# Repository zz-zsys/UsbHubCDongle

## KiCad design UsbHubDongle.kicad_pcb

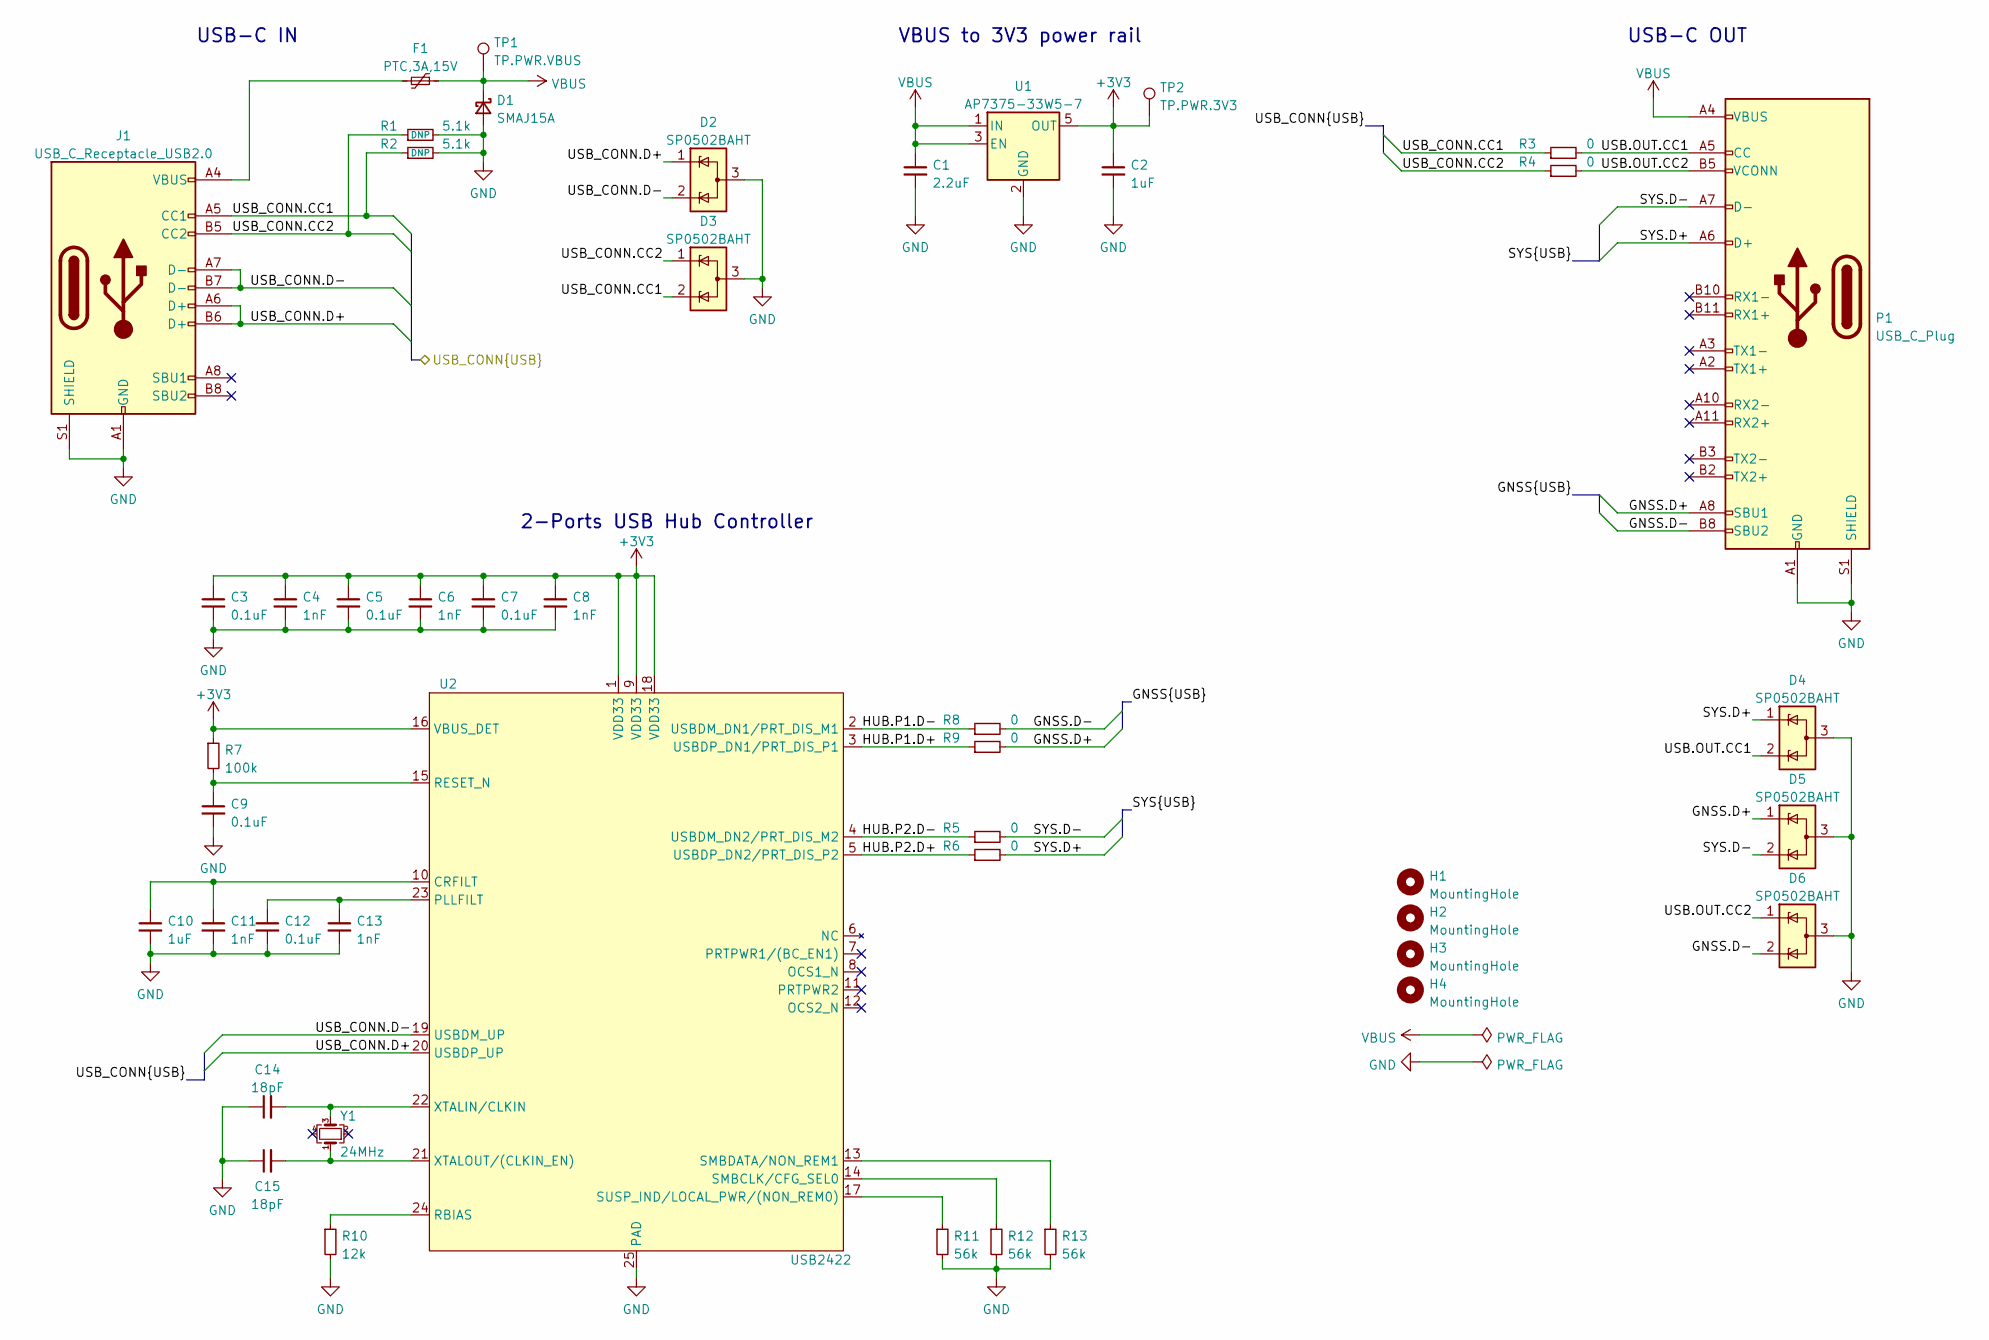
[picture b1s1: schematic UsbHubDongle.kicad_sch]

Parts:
C1: 2.2uF; C_0603_1608Metric
C2, C10: 1uF; C_0603_1608Metric
C3, C5, C7, C9, C12: 0.1uF; C_0603_1608Metric
C4, C6, C8, C11, C13: 1nF; C_0603_1608Metric
C14, C15: 18pF; C_0603_1608Metric
D1: SMAJ15A; D_SMA
D2, D3, D4, D5, D6: SP0502BAHT; SOT-23
F1: PTC,3A,15V; Fuse_2920_7451Metric
H1, H2, H3, H4: MountingHole; MountingHole_2.7mm_M2.5
J1: USB_C_Receptacle_USB2.0; USB_C_Receptacle_GCT_USB4105-xx-A_16P_TopMnt_Horizontal
P1: USB_C_Plug; USB_C_Plug_GCT_USB4155-03-C
R1, R2: 5.1k; R_0603_1608Metric
R3, R4, R5, R6, R8, R9: 0; R_0603_1608Metric
R7: 100k; R_0603_1608Metric
R10: 12k; R_0603_1608Metric
R11, R12, R13: 56k; R_0603_1608Metric
TP1: TP.PWR.VBUS; TestPoint_Loop_D1.80mm_Drill1.0mm_Beaded
TP2: TP.PWR.3V3; TestPoint_Loop_D1.80mm_Drill1.0mm_Beaded
U1: AP7375-33W5-7; SOT-23-5
U2: USB2422; QFN-24-1EP_4x4mm_P0.5mm_EP2.5x2.5mm_ThermalVias
Y1: 24MHz; Crystal_SMD_2016-4Pin_2.0x1.6mm

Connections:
+3V3: C2.1, C3.1, C4.1, C5.1, C6.1, C7.1, C8.1, R7.1, TP2.1, U1.5 (OUT), U2.1 (VDD33), U2.9 (VDD33), U2.16 (VBUS_DET), U2.18 (VDD33)
/GNSS.D+: D5.1 (K), P1.A8 (SBU1), R9.2
/GNSS.D-: D6.2 (K), P1.B8 (SBU2), R8.2
/HUB.P1.D+: R9.1, U2.3 (USBDP_DN1/PRT_DIS_P1)
/HUB.P1.D-: R8.1, U2.2 (USBDM_DN1/PRT_DIS_M1)
/HUB.P2.D+: R6.1, U2.5 (USBDP_DN2/PRT_DIS_P2)
/HUB.P2.D-: R5.1, U2.4 (USBDM_DN2/PRT_DIS_M2)
/SYS.D+: D4.1 (K), P1.A6 (D+), P1.B6 (D+), R6.2
/SYS.D-: D5.2 (K), P1.A7 (D-), P1.B7 (D-), R5.2
/USB.OUT.CC1: D4.2 (K), P1.A5 (CC), R3.2
/USB.OUT.CC2: D6.1 (K), P1.B5 (VCONN), R4.2
/USB_CONN.CC1: D3.2 (K), J1.A5 (CC1), R2.1, R3.1
/USB_CONN.CC2: D3.1 (K), J1.B5 (CC2), R1.1, R4.1
/USB_CONN.D+: D2.1 (K), J1.A6 (D+), J1.B6 (D+), U2.20 (USBDP_UP)
/USB_CONN.D-: D2.2 (K), J1.A7 (D-), J1.B7 (D-), U2.19 (USBDM_UP)
GND: C1.2, C2.2, C3.2, C4.2, C5.2, C6.2, C7.2, C8.2, C9.2, C10.2, C11.2, C12.2, C13.2, C14.1, C15.1, D1.2 (A), D2.3 (A), D3.3 (A), D4.3 (A), D5.3 (A), D6.3 (A), J1.A1 (GND), J1.A12 (GND), J1.B1 (GND), J1.B12 (GND), J1.S1 (SHIELD), P1.A1 (GND), P1.A12 (GND), P1.B1 (GND), P1.B12 (GND), P1.S1 (SHIELD), R1.2, R2.2, R10.2, R11.2, R12.2, R13.2, U1.2 (GND), U2.25 (PAD)
unnamed: C9.1, R7.2, U2.15 (RESET_N)
unnamed: C10.1, C11.1, U2.10 (CRFILT)
unnamed: C12.1, C13.1, U2.23 (PLLFILT)
unnamed: C14.2, U2.22 (XTALIN/CLKIN), Y1.3
unnamed: C15.2, U2.21 (XTALOUT/(CLKIN_EN)), Y1.1
unnamed: F1.2, J1.A4 (VBUS), J1.A9 (VBUS), J1.B4 (VBUS), J1.B9 (VBUS)
unnamed: R10.1, U2.24 (RBIAS)
unnamed: R11.1, U2.17 (SUSP_IND/LOCAL_PWR/(NON_REM0))
unnamed: R12.1, U2.14 (SMBCLK/CFG_SEL0)
unnamed: R13.1, U2.13 (SMBDATA/NON_REM1)
VBUS: C1.1, D1.1 (K), F1.1, P1.A4 (VBUS), P1.A9 (VBUS), P1.B4 (VBUS), P1.B9 (VBUS), TP1.1, U1.1 (IN), U1.3 (EN)

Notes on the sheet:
2-Ports USB Hub Controller
USB-C IN
USB-C OUT
VBUS to 3V3 power rail

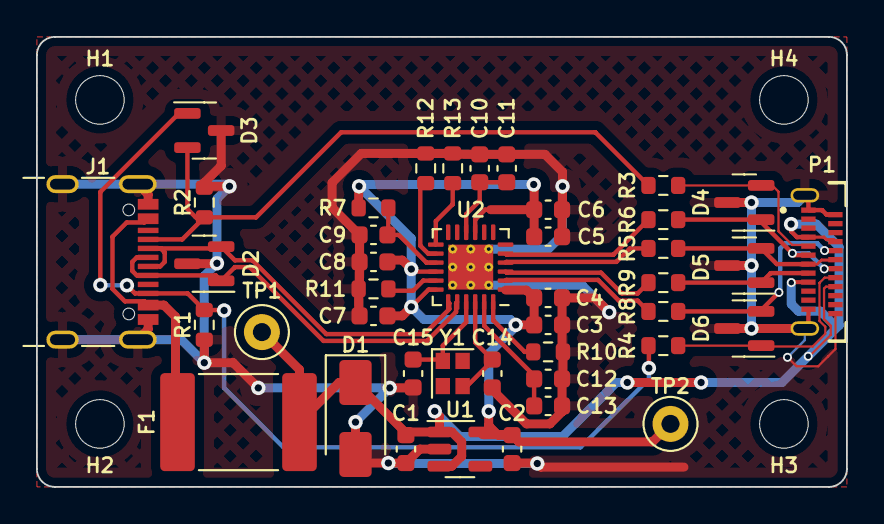
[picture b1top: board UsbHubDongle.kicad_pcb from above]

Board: 2 copper layers, 45.0 x 25.0 mm, 46 parts (0 on the bottom side), 27 nets.

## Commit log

2023-03-27 improve the differential pair lines, and increase the min via holes size from 0,2 to 0,3mm
